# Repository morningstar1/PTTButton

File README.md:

# PTTButton

## One Button Keyboard

A minimalistic keyboard with just one button.

Inspiered by [fnrow](https://github.com/dinofizz/fnrow-pcb) from Dino Fizzotti.

It uses USB Type C for uplink and has an additional USB Type A downlink port.

Currently uses QMK software from fnrow.

Used Chips:
 * [STM32F042G6U6](docs/stm32f042g6.pdf) Microcontroler
 * [Microchip USB2422](docs/00001726B.pdf) Two Port USB 2.0 Hub
 * [Texas Instruments TPS2051](docs/tps2051.pdf) USB Power Switch

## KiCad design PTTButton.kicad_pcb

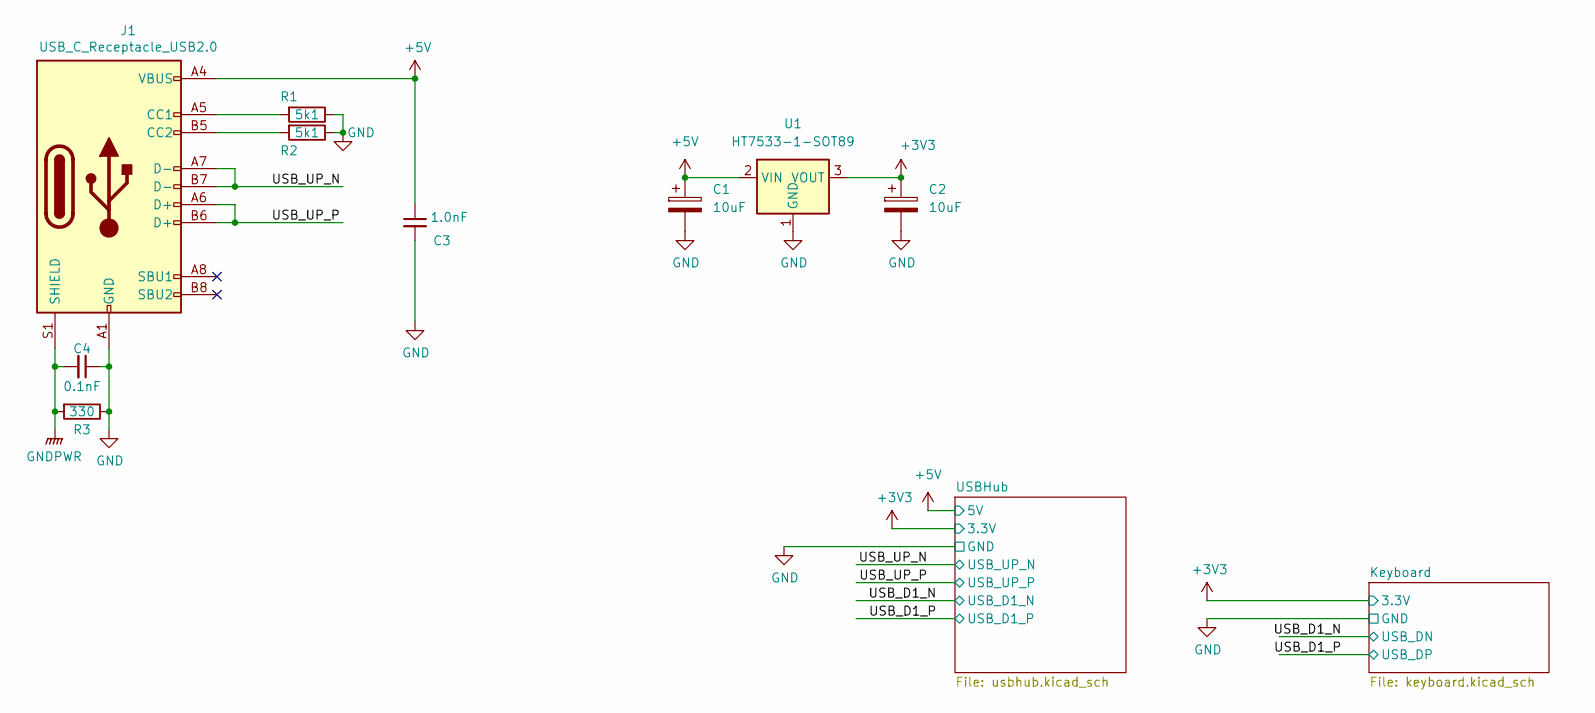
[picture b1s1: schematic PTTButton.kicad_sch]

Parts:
C1, C2: 10uF; CP_EIA-3216-18_Kemet-A
C3: 1.0nF; C_0603_1608Metric
C4: 0.1nF; C_0603_1608Metric
J1: USB_C_Receptacle_USB2.0; USB_C_Receptacle_HRO_TYPE-C-31-M-12
R1, R2: 5k1; R_0603_1608Metric_Pad0.98x0.95mm_HandSolder
R3: 330; R_0603_1608Metric_Pad0.98x0.95mm_HandSolder
U1: HT7533-1-SOT89; SOT-89-3

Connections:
+3V3: C2.1, U1.3 (VOUT); also elsewhere on the board
+5V: C1.1, C3.1, J1.A4 (VBUS), J1.A9 (VBUS), J1.B4 (VBUS), J1.B9 (VBUS), U1.2 (VIN); also elsewhere on the board
/USB_UP_N: J1.A7 (D-), J1.B7 (D-); also elsewhere on the board
/USB_UP_P: J1.A6 (D+), J1.B6 (D+); also elsewhere on the board
GND: C1.2, C2.2, C3.2, C4.1, J1.A1 (GND), J1.A12 (GND), J1.B1 (GND), J1.B12 (GND), R1.1, R2.1, R3.1, U1.1 (GND); also elsewhere on the board
GNDPWR: C4.2, J1.S1 (SHIELD), R3.2; also elsewhere on the board
unnamed: J1.A5 (CC1), R1.2
unnamed: J1.B5 (CC2), R2.2

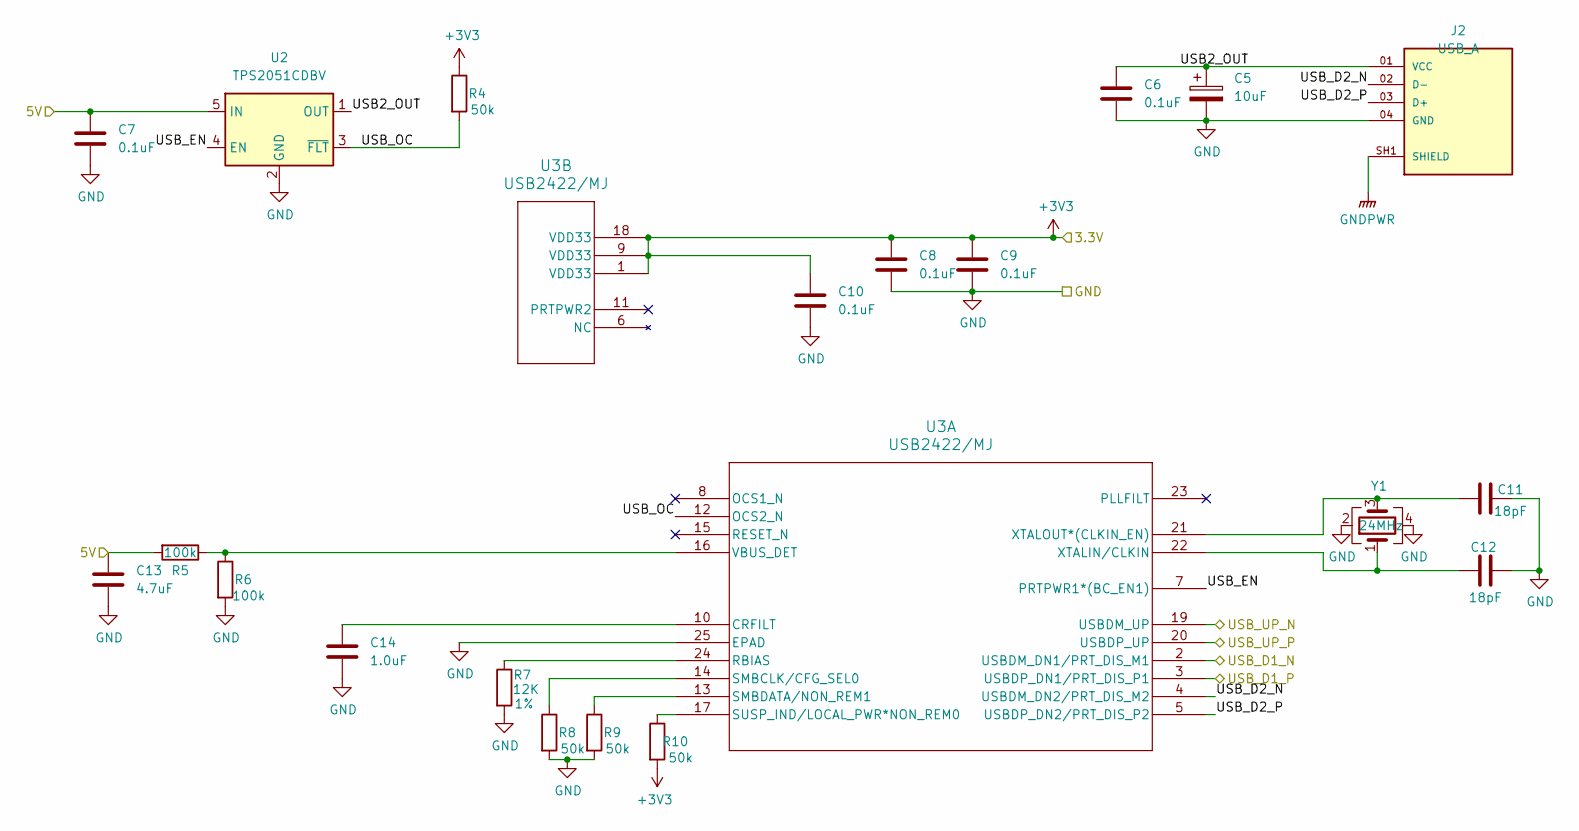
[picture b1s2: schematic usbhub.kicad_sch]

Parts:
C5: 10uF; CP_EIA-3216-18_Kemet-A
C6, C7, C8, C9, C10: 0.1uF; C_0603_1608Metric
C11, C12: 18pF; C_0603_1608Metric
C13: 4.7uF; C_0603_1608Metric
C14: 1.0uF; C_0603_1608Metric
J2: USB_A; AMPHENOL_87583-2010BLF; PARTREV AD; DigiKey_Part_Number 609-4413-ND
R4, R8, R9, R10: 50k; R_0603_1608Metric_Pad0.98x0.95mm_HandSolder
R5, R6: 100k; R_0603_1608Metric_Pad0.98x0.95mm_HandSolder
R7: 12K; R_0603_1608Metric_Pad0.98x0.95mm_HandSolder
U2: TPS2051CDBV; SOT-23-5
U3: USB2422/MJ; SQFN24_4X4MC_MCH
Y1: 24MHz; Crystal_SMD_2520-4Pin_2.5x2.0mm

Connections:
+3V3: C8.1, C9.1, C10.1, R4.1, R10.2, U3.1 (VDD33), U3.9 (VDD33), U3.18 (VDD33); also elsewhere on the board
+5V: C7.1, C13.1, R5.2, U2.5 (IN); also elsewhere on the board
/USBHub/USB2_OUT: C5.1, C6.1, J2.01 (VCC), U2.1 (OUT)
/USBHub/USB_D2_N: J2.02 (D-), U3.4 (USBDM_DN2/PRT_DIS_M2)
/USBHub/USB_D2_P: J2.03 (D+), U3.5 (USBDP_DN2/PRT_DIS_P2)
/USBHub/USB_EN: U2.4 (EN), U3.7 (PRTPWR1*(BC_EN1))
/USBHub/USB_OC: R4.2, U2.3 (~FLT), U3.12 (OCS2_N)
/USB_D1_N: U3.2 (USBDM_DN1/PRT_DIS_M1); also elsewhere on the board
/USB_D1_P: U3.3 (USBDP_DN1/PRT_DIS_P1); also elsewhere on the board
/USB_UP_N: U3.19 (USBDM_UP); also elsewhere on the board
/USB_UP_P: U3.20 (USBDP_UP); also elsewhere on the board
GND: C5.2, C6.2, C7.2, C8.2, C9.2, C10.2, C11.2, C12.2, C13.2, C14.2, J2.04 (GND), R6.2, R7.2, R8.2, R9.2, U2.2 (GND), U3.25 (EPAD), Y1.2, Y1.4; also elsewhere on the board
GNDPWR: J2.SH1 (SHIELD), J2.SH2 (SHIELD); also elsewhere on the board
unnamed: C14.1, U3.10 (CRFILT)
unnamed: R7.1, U3.24 (RBIAS)
unnamed: R8.1, U3.14 (SMBCLK/CFG_SEL0)
unnamed: R9.1, U3.13 (SMBDATA/NON_REM1)
unnamed: R10.1, U3.17 (SUSP_IND/LOCAL_PWR*NON_REM0)
unnamed: R5.1, R6.1, U3.16 (VBUS_DET)
unnamed: C12.1, U3.22 (XTALIN/CLKIN), Y1.1
unnamed: C11.1, U3.21 (XTALOUT*(CLKIN_EN)), Y1.3

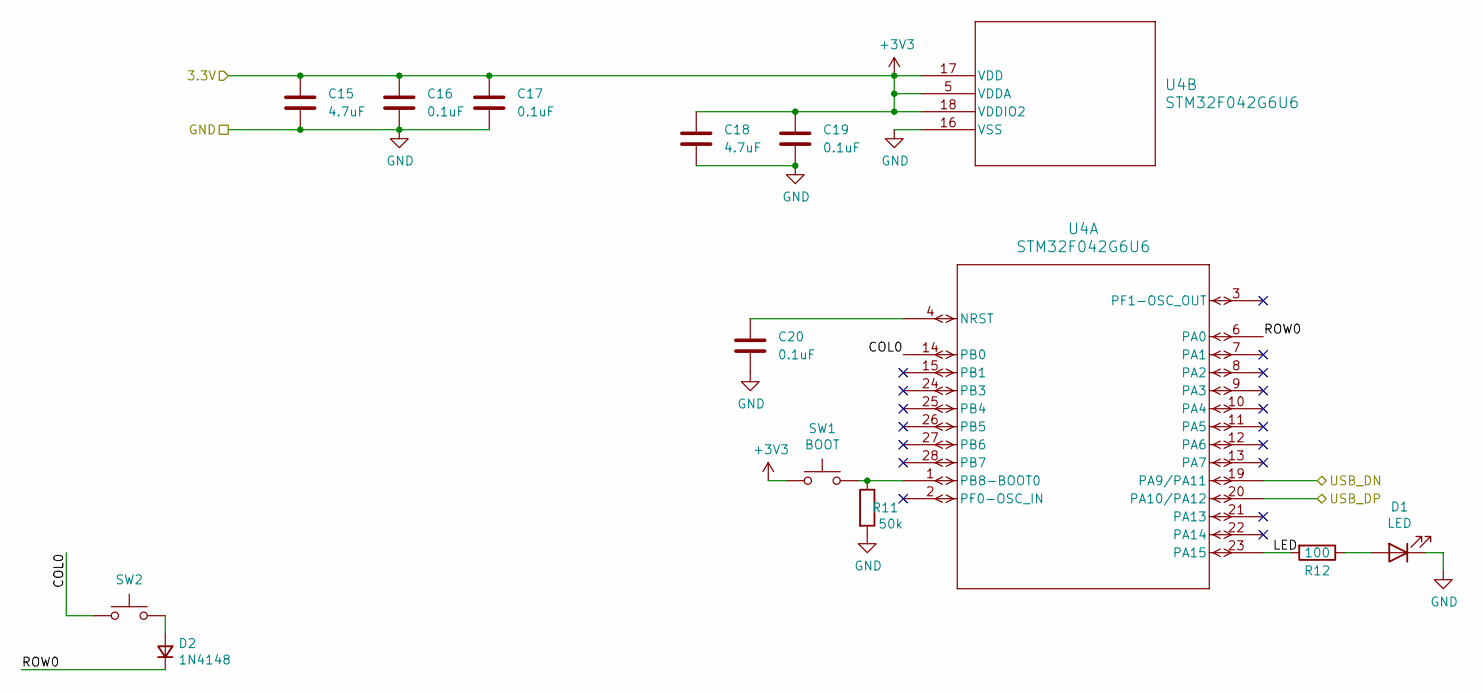
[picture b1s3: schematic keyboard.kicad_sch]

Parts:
C15, C18: 4.7uF; C_0603_1608Metric
C16, C17, C19, C20: 0.1uF; C_0603_1608Metric
D1: LED; LED_0805_2012Metric_Pad1.15x1.40mm_HandSolder; JLCPCB C2297
D2: 1N4148; D_SOD-123
R11: 50k; R_0603_1608Metric_Pad0.98x0.95mm_HandSolder
R12: 100; R_0603_1608Metric_Pad0.98x0.95mm_HandSolder
SW1: BOOT; SW_SPST_TS-1088-xR020; JLCPCB C720477
SW2: SW_Push; MX100H
U4: STM32F042G6U6; UFQFPN28-4x4mm

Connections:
+3V3: C15.1, C16.1, C17.1, C18.1, C19.1, SW1.1, U4.5 (VDDA), U4.17 (VDD), U4.18 (VDDIO2); also elsewhere on the board
/Keyboard/COL0: SW2.2, U4.14 (PB0)
/Keyboard/LED: R12.2, U4.23 (PA15)
/Keyboard/ROW0: D2.1 (K), U4.6 (PA0)
/USB_D1_N: U4.19 (PA9/PA11); also elsewhere on the board
/USB_D1_P: U4.20 (PA10/PA12); also elsewhere on the board
GND: C15.2, C16.2, C17.2, C18.2, C19.2, C20.2, D1.1 (K), R11.2, U4.16 (VSS); also elsewhere on the board
unnamed: D1.2 (A), R12.1
unnamed: D2.2 (A), SW2.1
unnamed: C20.1, U4.4 (NRST)
unnamed: R11.1, SW1.2, U4.1 (PB8-BOOT0)

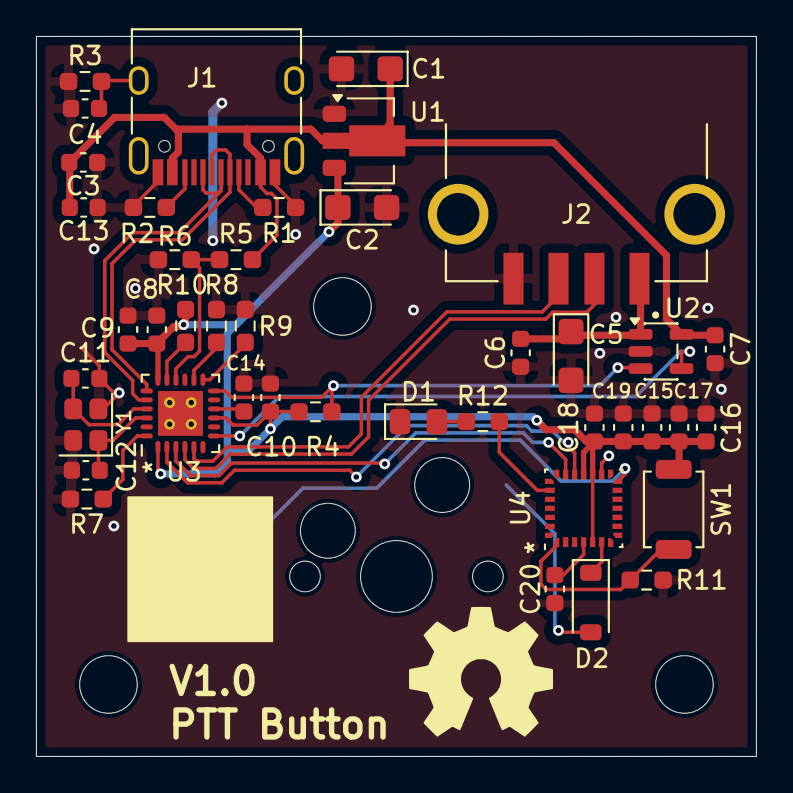
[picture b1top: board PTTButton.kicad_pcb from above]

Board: 2 copper layers, 40.0 x 40.0 mm, 43 parts (1 on the bottom side), 30 nets.

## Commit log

2026-01-04 First Release
2026-01-10 Update Case Sizes
2026-01-16 enlarge thredded insert hole
